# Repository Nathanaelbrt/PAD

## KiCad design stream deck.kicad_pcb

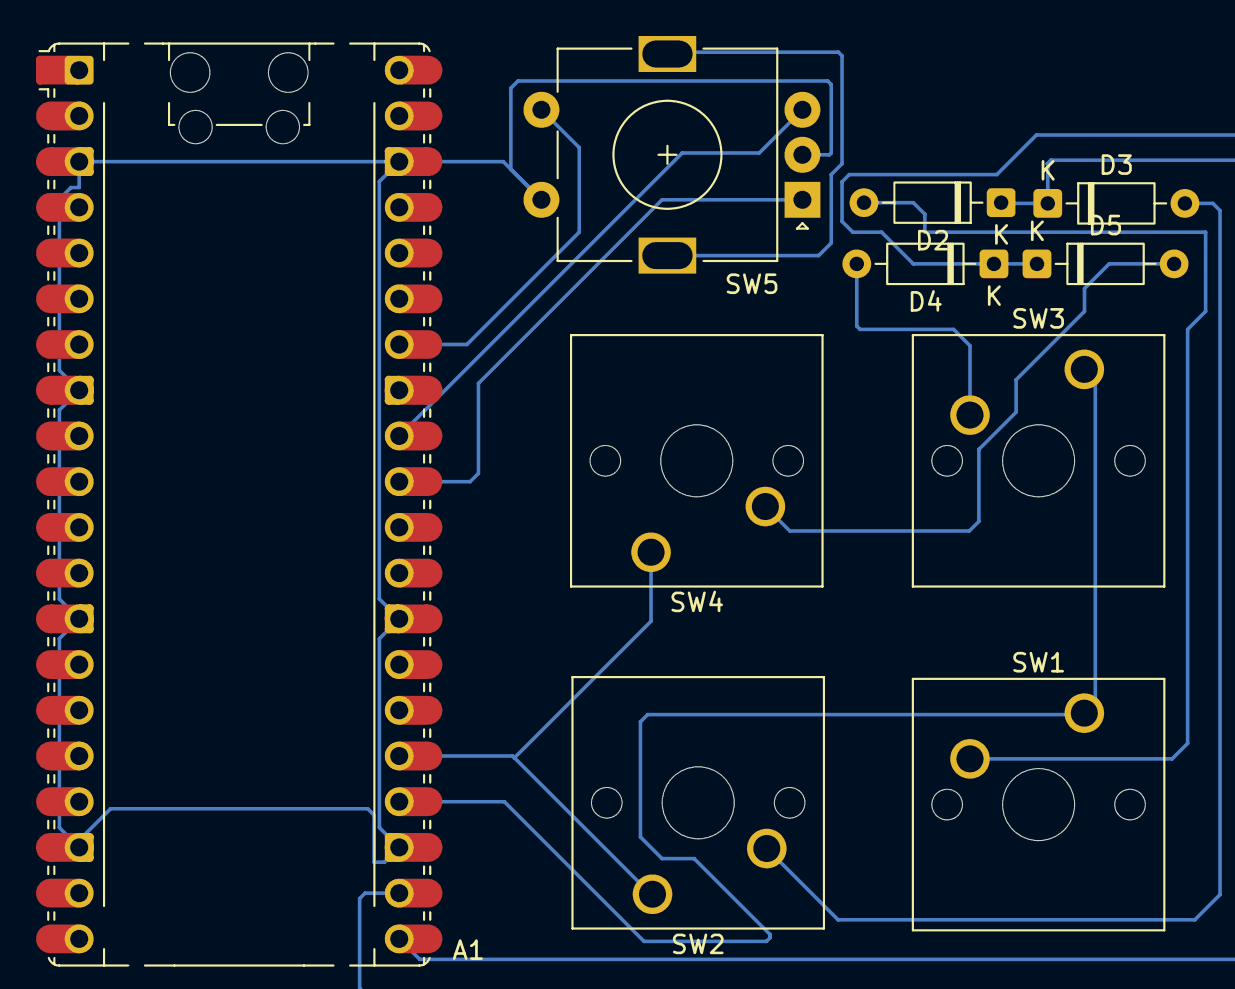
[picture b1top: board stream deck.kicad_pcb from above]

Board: 2 copper layers, 10 parts (0 on the bottom side), 12 nets.

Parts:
A1: RaspberryPi_Pico; RaspberryPi_Pico_Common_Unspecified
D2, D3, D4, D5: 1N4148; D_DO-35_SOD27_P7.62mm_Horizontal
SW1, SW2, SW3, SW4: SW_Push_45deg; SW_Cherry_MX_1.00u_PCB
SW5: RotaryEncoder_Switch_MP; RotaryEncoder_Alps_EC11E-Switch_Vertical_H20mm

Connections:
unnamed: A1.3 (GND), A1.8 (GND), A1.13 (GND), A1.18 (GND), A1.23 (GND), A1.28 (GND), A1.38 (GND), SW5.C, SW5.S2
unnamed: A1.21 (GPIO16), D2.1 (K), D3.1 (K)
unnamed: A1.22 (GPIO17), D4.1 (K), D5.1 (K)
unnamed: A1.24 (GPIO18), SW1.1, SW3.1
unnamed: A1.25 (GPIO19), SW2.1, SW4.1
unnamed: A1.31 (GPIO26_ADC0), SW5.A
unnamed: A1.32 (GPIO27_ADC1), SW5.B
unnamed: A1.34 (GPIO28_ADC2), SW5.S1
unnamed: D2.2 (A), SW1.2
unnamed: D3.2 (A), SW2.2
unnamed: D4.2 (A), SW3.2
unnamed: D5.2 (A), SW4.2
